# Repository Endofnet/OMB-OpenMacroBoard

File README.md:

# OMB-OpenMacroBoard

These are the PCB-Files for the OpenMacroBoard (O.M.B.) the O.M.B. is a 10-key, programmable keyboard.
It is meant to be used with the [OMB-OpenMacroBoardFirmware](https://github.com/Endofnet/OMB-OpenMacroBoard-Firmware "OMB-Firmware on GitHub").<br/>
As the board uses an Atmega32u4 it should be possible to use it with QMK if ported, but that is currently not implemented.
The first released version of the O.M.B. is version 1.1.

## Features

* 10 mechanical keys
* individual rgb lighting per key
* upcomming support for mini OLED-screens
* USB Type-C connector!
* custom expandable with breakout header

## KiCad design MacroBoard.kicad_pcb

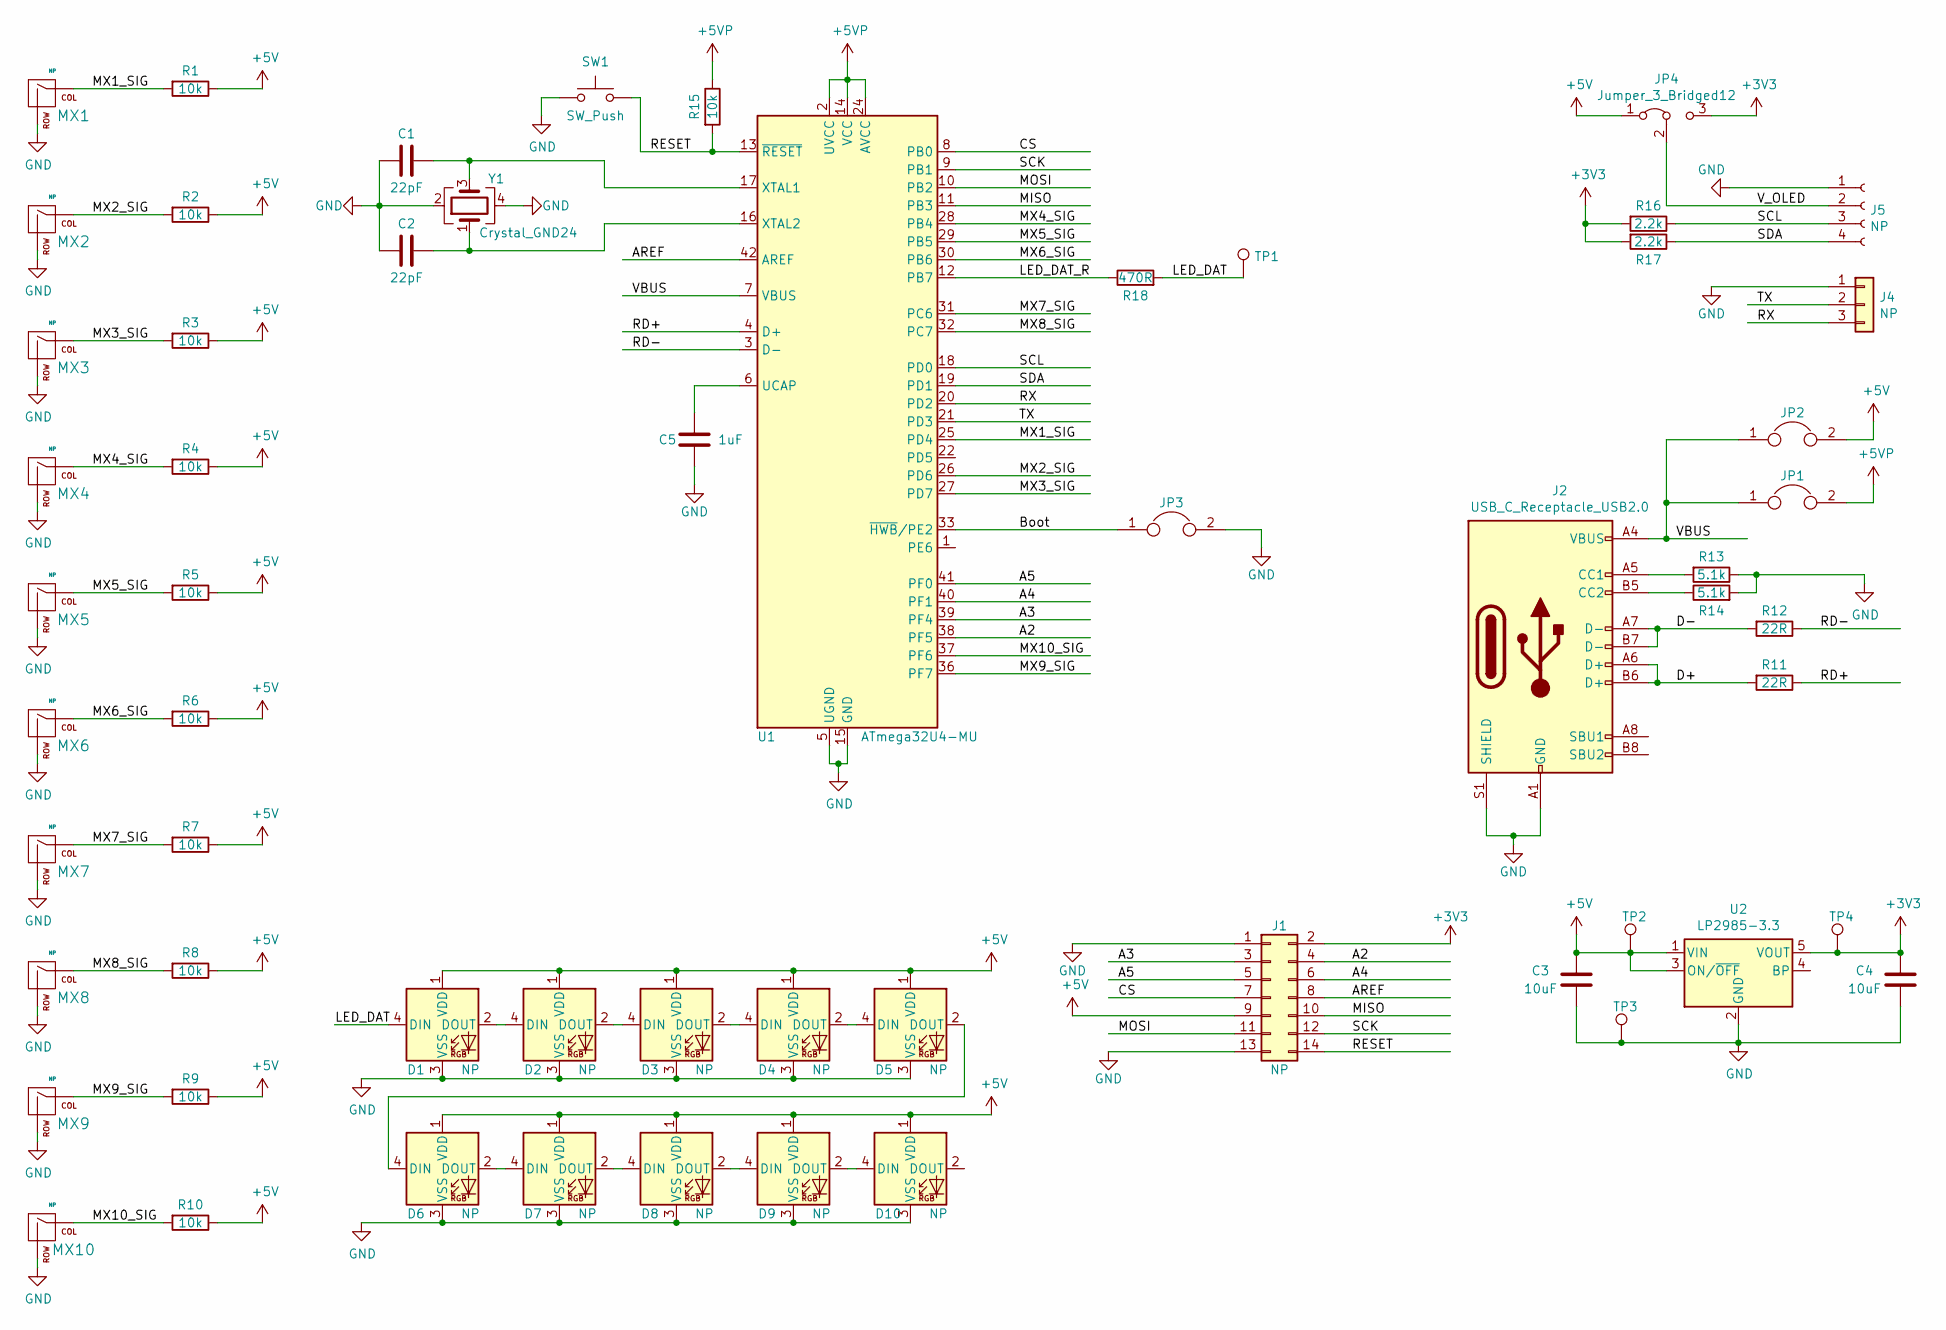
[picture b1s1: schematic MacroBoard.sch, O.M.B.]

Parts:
C1, C2: 22pF; C_0805_2012Metric; JLCID C15850
C3, C4: 10uF; C_0805_2012Metric; JLCID C15850
C5: 1uF; C_0805_2012Metric; JLCID C15850
D1, D2, D3, D4, D5, D6, D7, D8, D9, D10: NP; WS2812b_ThroughBoard
J1: NP; PinHeader_2x07_P2.54mm_Vertical
J2: USB_C_Receptacle_USB2.0; USB_C_Receptacle_GCT_USB4085
J4: NP; PinHeader_1x03_P2.54mm_Vertical
J5: NP; PinHeader_1x04_P2.54mm_Vertical
JP1, JP2, JP3: Jumper; SolderJumper-2_P1.3mm_Open_RoundedPad1.0x1.5mm
JP4: Jumper_3_Bridged12; SolderJumper-3_P1.3mm_Open_RoundedPad1.0x1.5mm
MX1, MX2, MX3, MX4, MX5, MX6, MX7, MX8, MX9, MX10: NP; SW_Cherry_MX_1.00u_PCB
R1, R2, R3, R4, R5, R6, R7, R8, R9, R10: 10k; R_0805_2012Metric_Pad1.15x1.40mm_HandSolder
R11, R12: 22R; R_0603_1608Metric_Pad1.05x0.95mm_HandSolder; JLCID C27834
R13, R14: 5.1k; R_0603_1608Metric_Pad1.05x0.95mm_HandSolder; JLCID C27834
R15: 10k; R_0603_1608Metric_Pad1.05x0.95mm_HandSolder; JLCID C17414
R16, R17: 2.2k; R_0603_1608Metric_Pad1.05x0.95mm_HandSolder; JLCID C17520
R18: 470R; R_0603_1608Metric_Pad1.05x0.95mm_HandSolder; JLCID C17710
SW1: SW_Push; SW_SPST_TL3342; JLCID C318884
TP1, TP2, TP3, TP4: TestPoint; TestPoint_Pad_D1.5mm
U1: ATmega32U4-MU; QFN-44-1EP_7x7mm_P0.5mm_EP5.2x5.2mm; JLCID C45874
U2: LP2985-3.3; SOT-23-5; JLCID C89826
Y1: Crystal_GND24; Crystal_SMD_3225-4Pin_3.2x2.5mm; JLCID C13738

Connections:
+3V3: C4.1, J1.2, JP4.3 (B), R16.2, R17.2, TP4.1, U2.5 (VOUT)
+5V: C3.1, D1.1 (VDD), D2.1 (VDD), D3.1 (VDD), D4.1 (VDD), D5.1 (VDD), D6.1 (VDD), D7.1 (VDD), D8.1 (VDD), D9.1 (VDD), D10.1 (VDD), J1.9, JP2.2, JP4.1 (A), R1.1, R2.1, R3.1, R4.1, R5.1, R6.1, R7.1, R8.1, R9.1, R10.1, TP2.1, U2.1 (VIN), U2.3 (ON/~OFF~)
+5VP: JP1.2, R15.1, U1.2 (UVCC), U1.14 (VCC), U1.24 (AVCC), U1.34 (VCC), U1.44 (AVCC)
/A2: J1.4, U1.38 (PF5)
/A3: J1.3, U1.39 (PF4)
/A4: J1.6, U1.40 (PF1)
/A5: J1.5, U1.41 (PF0)
/AREF: J1.8, U1.42 (AREF)
/Boot: JP3.1, U1.33 (~HWB~/PE2)
/CS: J1.7, U1.8 (PB0)
/D+: J2.A6 (D+), J2.B6 (D+), R11.2
/D-: J2.A7 (D-), J2.B7 (D-), R12.2
/LED_DAT: D1.4 (DIN), R18.2, TP1.1
/LED_DAT_R: R18.1, U1.12 (PB7)
/MISO: J1.10, U1.11 (PB3)
/MOSI: J1.11, U1.10 (PB2)
/MX1_SIG: MX1.1 (COL), R1.2, U1.25 (PD4)
/MX2_SIG: MX2.1 (COL), R2.2, U1.26 (PD6)
/MX3_SIG: MX3.1 (COL), R3.2, U1.27 (PD7)
/MX4_SIG: MX4.1 (COL), R4.2, U1.28 (PB4)
/MX5_SIG: MX5.1 (COL), R5.2, U1.29 (PB5)
/MX6_SIG: MX6.1 (COL), R6.2, U1.30 (PB6)
/MX7_SIG: MX7.1 (COL), R7.2, U1.31 (PC6)
/MX8_SIG: MX8.1 (COL), R8.2, U1.32 (PC7)
/MX9_SIG: MX9.1 (COL), R9.2, U1.36 (PF7)
/MX10_SIG: MX10.1 (COL), R10.2, U1.37 (PF6)
/RD+: R11.1, U1.4 (D+)
/RD-: R12.1, U1.3 (D-)
/RESET: J1.14, R15.2, SW1.2, U1.13 (~RESET)
/RX: J4.3, U1.20 (PD2)
/SCK: J1.12, U1.9 (PB1)
/SCL: J5.3, R16.1, U1.18 (PD0)
/SDA: J5.4, R17.1, U1.19 (PD1)
/TX: J4.2, U1.21 (PD3)
/VBUS: J2.A4 (VBUS), J2.A9 (VBUS), J2.B4 (VBUS), J2.B9 (VBUS), JP1.1, JP2.1, U1.7 (VBUS)
/V_OLED: J5.2, JP4.2 (C)
GND: C1.2, C2.2, C3.2, C4.2, C5.2, D1.3 (VSS), D2.3 (VSS), D3.3 (VSS), D4.3 (VSS), D5.3 (VSS), D6.3 (VSS), D7.3 (VSS), D8.3 (VSS), D9.3 (VSS), D10.3 (VSS), J1.1, J1.13, J2.A1 (GND), J2.A12 (GND), J2.B1 (GND), J2.B12 (GND), J2.S1 (SHIELD), J4.1, J5.1, JP3.2, MX1.2 (ROW), MX2.2 (ROW), MX3.2 (ROW), MX4.2 (ROW), MX5.2 (ROW), MX6.2 (ROW), MX7.2 (ROW), MX8.2 (ROW), MX9.2 (ROW), MX10.2 (ROW), R13.1, R14.2, SW1.1, TP3.1, U1.5 (UGND), U1.15 (GND), U1.23 (GND), U1.35 (GND), U1.43 (GND), U1.45 (GND), U2.2 (GND), Y1.2, Y1.4
unnamed: C1.1, U1.17 (XTAL1), Y1.3
unnamed: C2.1, U1.16 (XTAL2), Y1.1
unnamed: C5.1, U1.6 (UCAP)
unnamed: D1.2 (DOUT), D2.4 (DIN)
unnamed: D2.2 (DOUT), D3.4 (DIN)
unnamed: D3.2 (DOUT), D4.4 (DIN)
unnamed: D4.2 (DOUT), D5.4 (DIN)
unnamed: D5.2 (DOUT), D6.4 (DIN)
unnamed: D6.2 (DOUT), D7.4 (DIN)
unnamed: D7.2 (DOUT), D8.4 (DIN)
unnamed: D8.2 (DOUT), D9.4 (DIN)
unnamed: D9.2 (DOUT), D10.4 (DIN)
unnamed: J2.A5 (CC1), R13.2
unnamed: J2.B5 (CC2), R14.1

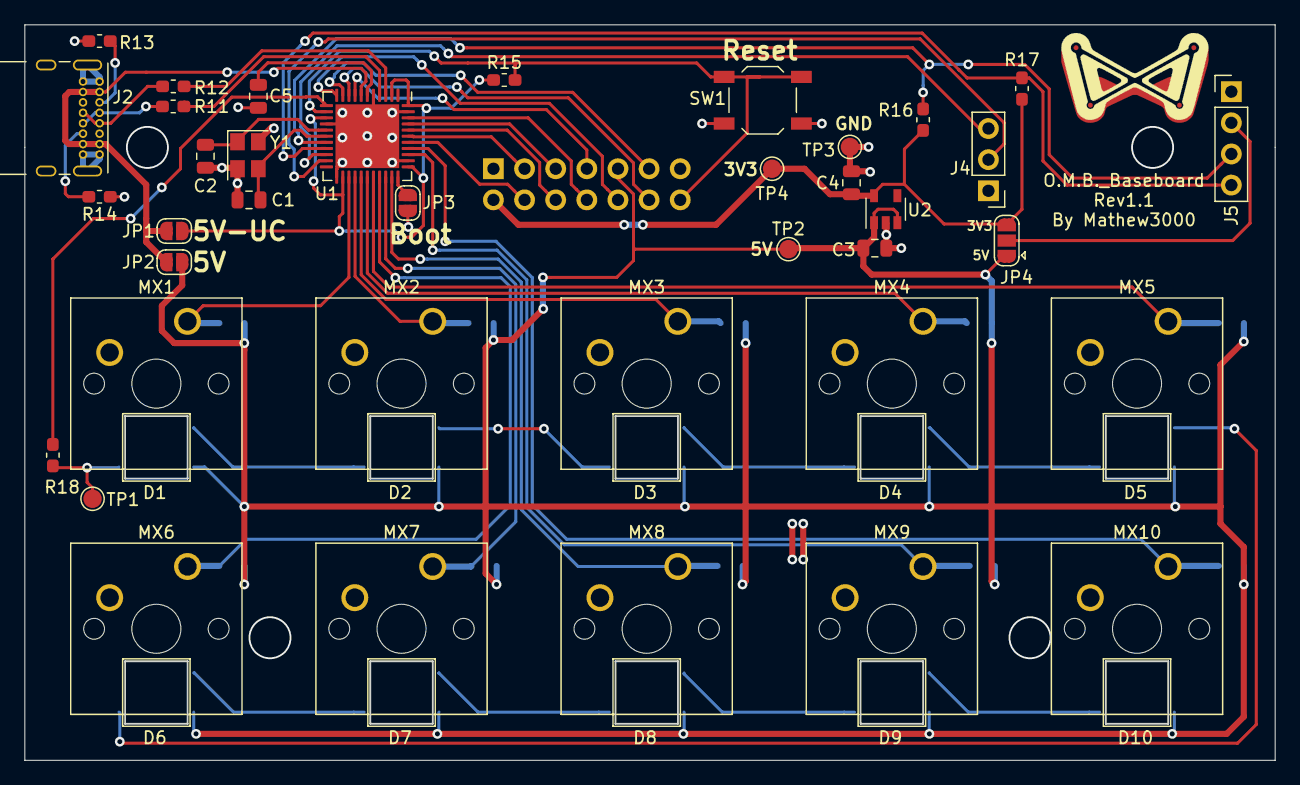
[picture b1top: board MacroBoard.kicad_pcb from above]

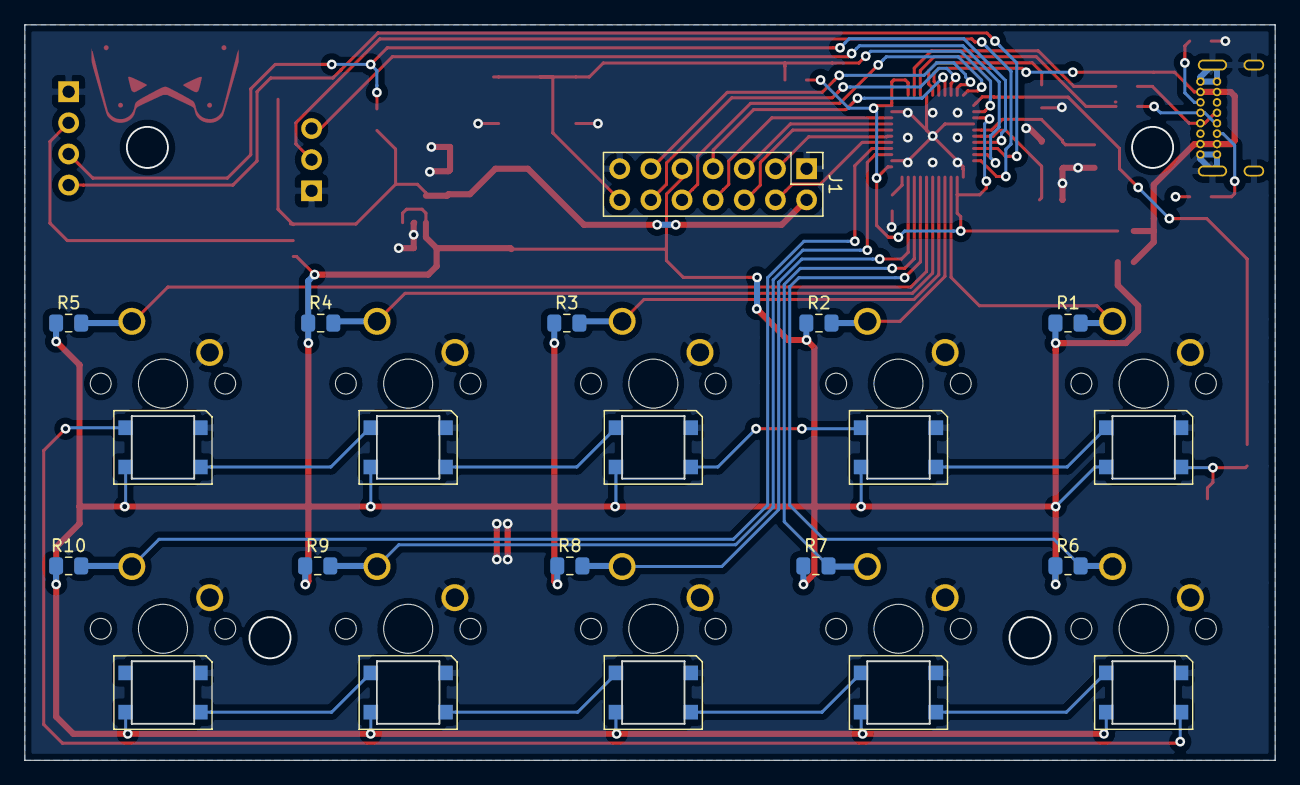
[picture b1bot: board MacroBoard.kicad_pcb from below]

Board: 2 copper layers, 102.0 x 60.0 mm, 60 parts (11 on the bottom side), 51 nets.

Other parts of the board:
Ref**: Val**; Logo_Color

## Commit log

2020-11-14 Initial Upload of V1.1
2020-11-14 Added O.M.B. Logo to PCB
2020-11-14 Added Preview image
2020-11-20 Removed 3 pin i2c connector and replaced it by 4 pin connector for oled attachment
2020-11-20 Readded Icon
2020-11-27 Removed output from tracking
2020-11-27 changed main header pinout to fit standard arduino/avr icsp header
2020-11-27 Removed Output.zip from tracking
